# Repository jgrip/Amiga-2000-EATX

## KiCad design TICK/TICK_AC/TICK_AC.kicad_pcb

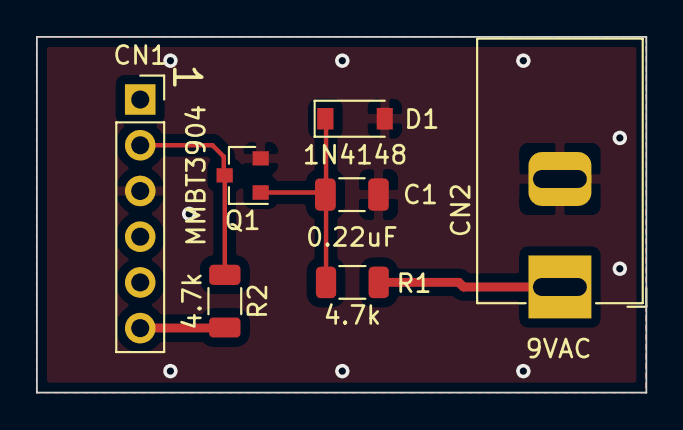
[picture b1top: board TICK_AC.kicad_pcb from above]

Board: 2 copper layers, 33.9 x 19.8 mm, 7 parts (0 on the bottom side), 5 nets.

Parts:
C1: 0.22uF; C_1206_3216Metric
CN1: To_Amiga; PinSocket_1x06_P2.54mm_Vertical
CN2: Barrel_Jack; BarrelJack_Horizontal
D1: 1N4148; D_SOD-123
Q1: MMBT3904; SOT-23
R1, R2: 4.7k; R_1206_3216Metric

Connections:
+5V: CN1.6, R2.2
/+9VAC: CN2.1, R1.2
/TBASE: CN1.2, Q1.3, R2.1
GND: C1.2, CN1.3, CN2.2, D1.2, Q1.2
unnamed: C1.1, D1.1, Q1.1, R1.1

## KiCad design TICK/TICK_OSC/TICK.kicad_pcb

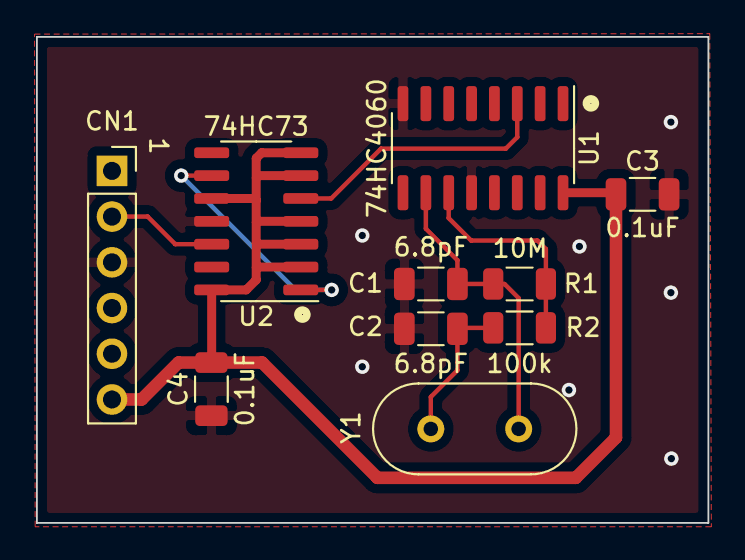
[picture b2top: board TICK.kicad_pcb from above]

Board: 2 copper layers, 37.3 x 27.0 mm, 10 parts (0 on the bottom side), 8 nets.

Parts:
C1, C2: 6.8pF; C_1206_3216Metric
C3, C4: 0.1uF; C_1206_3216Metric
CN1: To_Amiga; PinSocket_1x06_P2.54mm_Vertical
R1: 10M; R_1206_3216Metric
R2: 100k; R_1206_3216Metric
U1: 74HC4060; SOIC-16_3.9x9.9mm_P1.27mm
U2: 74HC73; SOIC-14_3.9x8.7mm_P1.27mm
Y1: 3.93216MHz; Crystal_HC49-U_Vertical

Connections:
+5V: C3.1, C4.2, CN1.6, U1.16, U2.2, U2.3, U2.4, U2.6, U2.7, U2.10, U2.14
/TBASE: CN1.2, U2.12
GND: C1.2, C2.2, C3.2, C4.1, CN1.3, U1.8, U1.12, U2.11
unnamed: C1.1, R1.1, U1.10, Y1.1
unnamed: C2.1, R2.2, Y1.2
unnamed: R1.2, R2.1, U1.11
unnamed: U1.3, U2.5
unnamed: U2.1, U2.9
